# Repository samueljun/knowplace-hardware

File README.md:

sr-sryrs_home_automation
========================

CS 130 Sr. Sryrs Home Automation IBM Project

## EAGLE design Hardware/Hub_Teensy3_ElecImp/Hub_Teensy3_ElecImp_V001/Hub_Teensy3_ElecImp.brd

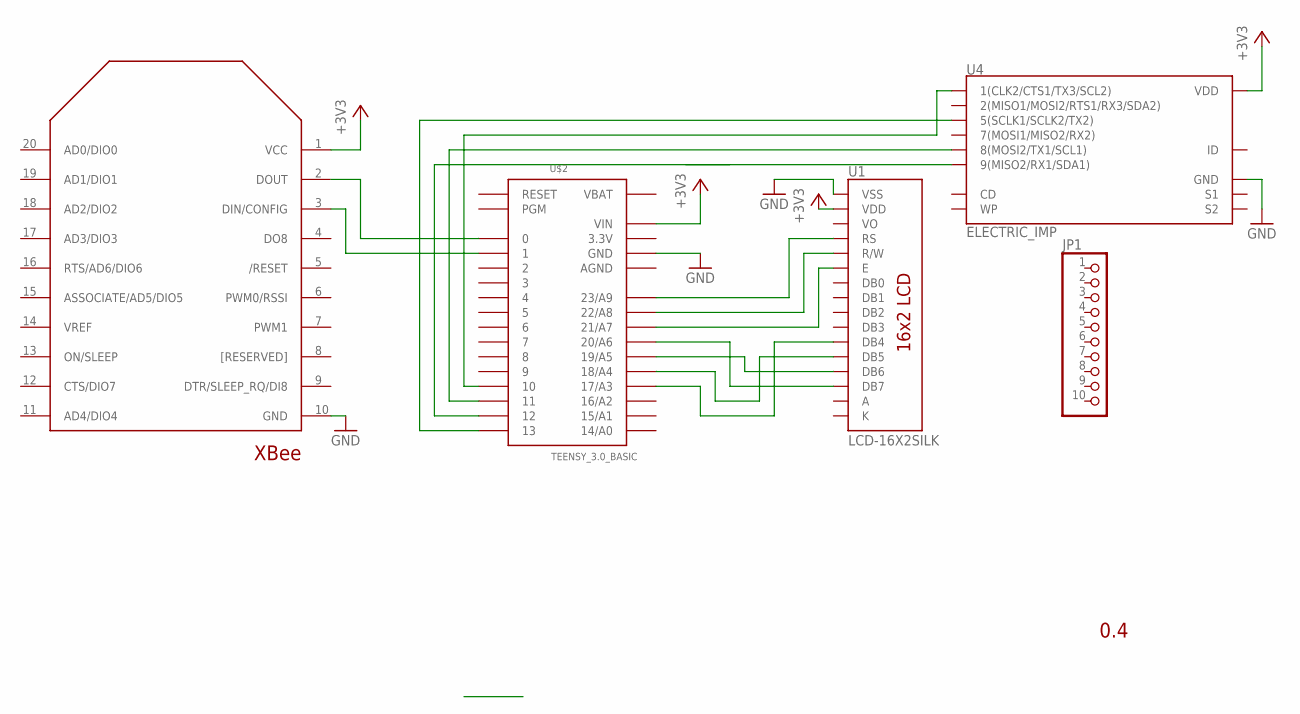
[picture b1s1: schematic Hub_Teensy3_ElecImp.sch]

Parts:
JP1: PINHD-1X10; 1X10
U1: LCD-16X2SILK; LCD-16X2
U4: ELECTRIC_IMP; SD_MMC_SOCKET
U$1: XBEE
U$2: TEENSY_3.0_BASIC

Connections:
3.3V: U$2.3.3V, U$2.3.3V1 (3.3V)
+3V3: U1.2 (VDD), U4.4 (VDD), U$1.1 (VCC), U$2.VIN
A: U1.15 (A)
AGND: U$2.AGND
GND: U1.1 (VSS), U4.3 (GND), U$1.10 (GND), U$2.GND, U$2.GND1 (GND)
K: U1.16 (K)
unnamed: U1.14 (DB7), U$2.20/A6
unnamed: U1.13 (DB6), U$2.19/A5
unnamed: U1.12 (DB5), U$2.18/A4
unnamed: U1.6 (E), U$2.21/A7
unnamed: U1.4 (RS), U$2.23/A9
unnamed: U1.5 (R/W), U$2.22/A8
unnamed: U4.5 (5(SCLK1/SCLK2/TX2)), U$2.13
unnamed: U4.1 (1(CLK2/CTS1/TX3/SCL2)), U$2.10
unnamed: U1.11 (DB4), U$2.17/A3
unnamed: U4.9 (9(MISO2/RX1/SDA1)), U$2.12
unnamed: U$1.3 (DIN/CONFIG), U$2.1
unnamed: U4.8 (8(MOSI2/TX1/SCL1)), U$2.11
unnamed: U$1.2 (DOUT), U$2.0
VBAT: U$2.VBAT

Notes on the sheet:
0.4

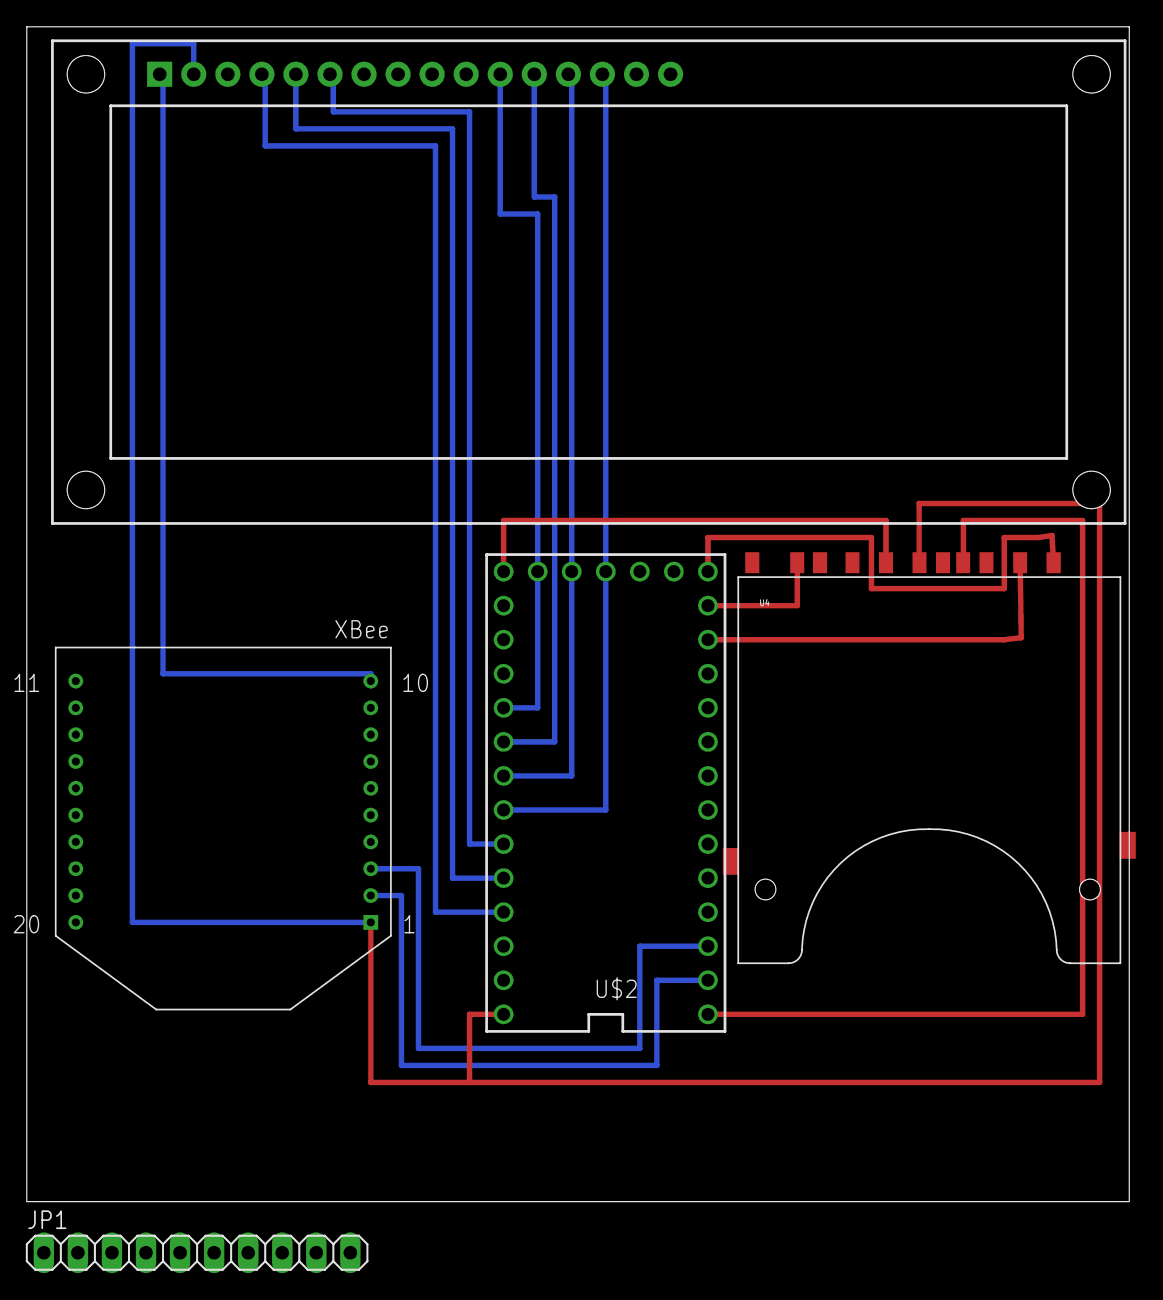
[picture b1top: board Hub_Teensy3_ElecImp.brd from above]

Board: 2 copper layers, 82.2 x 87.6 mm, 5 parts (0 on the bottom side), 16 nets.

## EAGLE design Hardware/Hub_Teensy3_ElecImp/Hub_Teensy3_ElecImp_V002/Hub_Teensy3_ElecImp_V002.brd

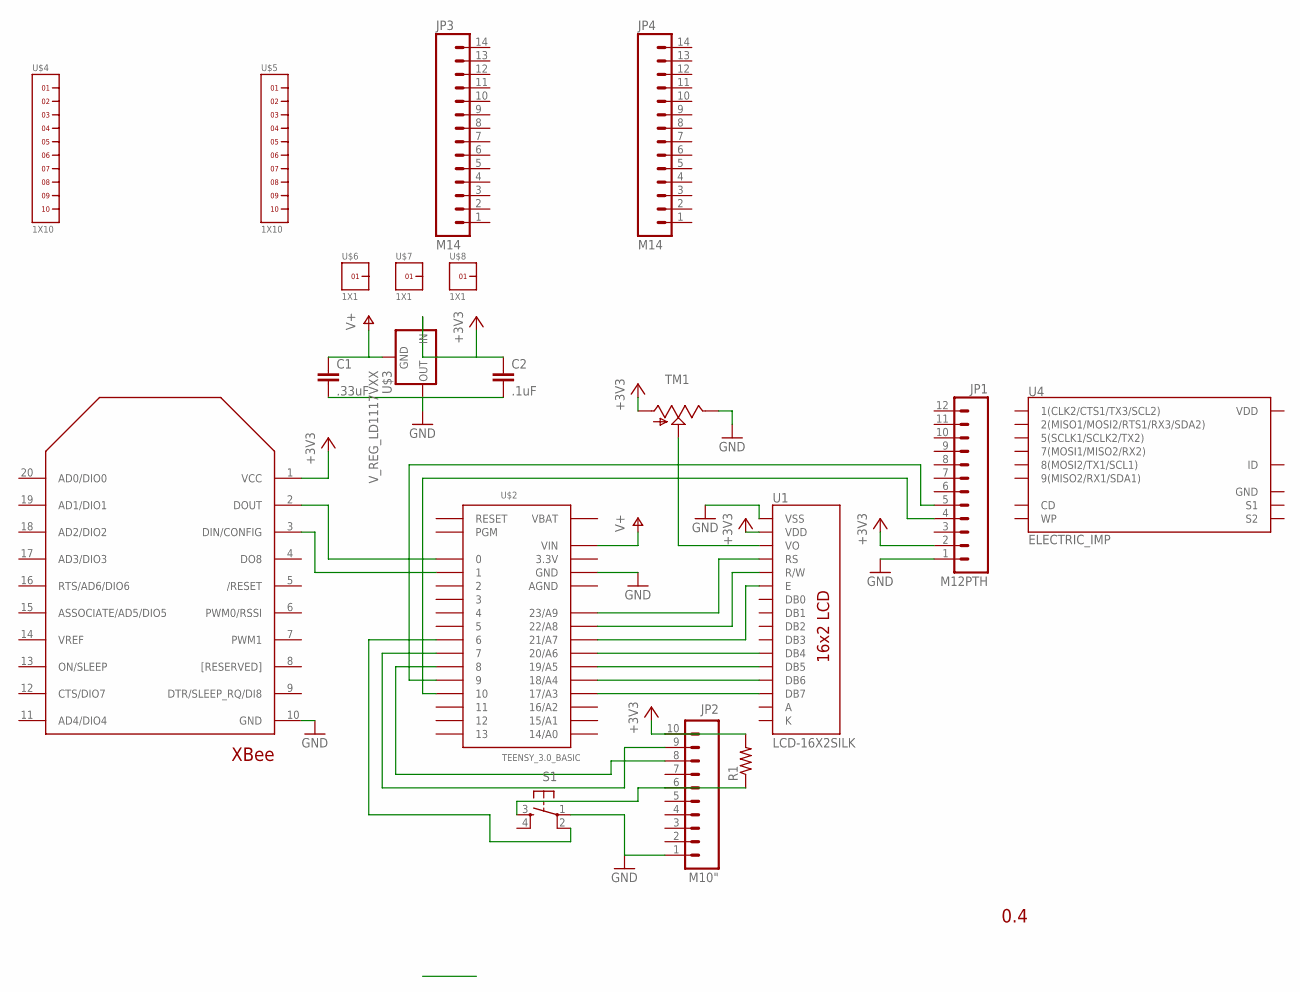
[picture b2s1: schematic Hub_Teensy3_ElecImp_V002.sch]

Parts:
C1: .33uF; 0805
C2: .1uF; 0805
JP1: M12PTH; 1X12
JP2: M10"; 1X10
JP3, JP4: M14; 1X14
R1: RESISTORPTH-1/4W; AXIAL-0.4
S1: TAC_SWITCHPTH; TACTILE-PTH
TM1: TRIM; 6MM
U1: LCD-16X2SILK; LCD-16X2
U4: ELECTRIC_IMP; SD_MMC_SOCKET
U$1: XBEE
U$2: TEENSY_3.0_BASIC
U$3: V_REG_LD1117VXX; 78XXL
U$4, U$5: 1X10
U$6, U$7, U$8: 1X1

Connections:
3.3V: U$2.3.3V, U$2.3.3V1 (3.3V)
+3V3: C2.1, JP1.2, JP2.10, R1.P$2 (2), TM1.A, U1.2 (VDD), U$1.1 (VCC), U$3.OUT (IN)
A: U1.15 (A)
AGND: U$2.AGND
GND: C1.2, C2.2, JP1.1, JP2.1, S1.1, TM1.E, U1.1 (VSS), U$1.10 (GND), U$2.GND, U$2.GND1 (GND), U$3.GND (OUT)
K: U1.16 (K)
unnamed: U1.11 (DB4), U$2.20/A6
unnamed: U1.12 (DB5), U$2.19/A5
unnamed: U1.13 (DB6), U$2.18/A4
unnamed: U1.6 (E), U$2.21/A7
unnamed: U1.4 (RS), U$2.23/A9
unnamed: U1.5 (R/W), U$2.22/A8
unnamed: JP1.5, U$2.9
unnamed: JP1.4, U$2.10
unnamed: U1.14 (DB7), U$2.17/A3
unnamed: JP2.8, U$2.8
unnamed: U$1.3 (DIN/CONFIG), U$2.1
unnamed: JP2.9, U$2.7
unnamed: TM1.S, U1.3 (VO)
unnamed: U$1.2 (DOUT), U$2.0
unnamed: JP2.6, R1.P$1 (1), S1.3
unnamed: S1.2, U$2.6
V+: C1.1, U$2.VIN, U$3.IN (GND)
VBAT: U$2.VBAT

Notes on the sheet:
0.4

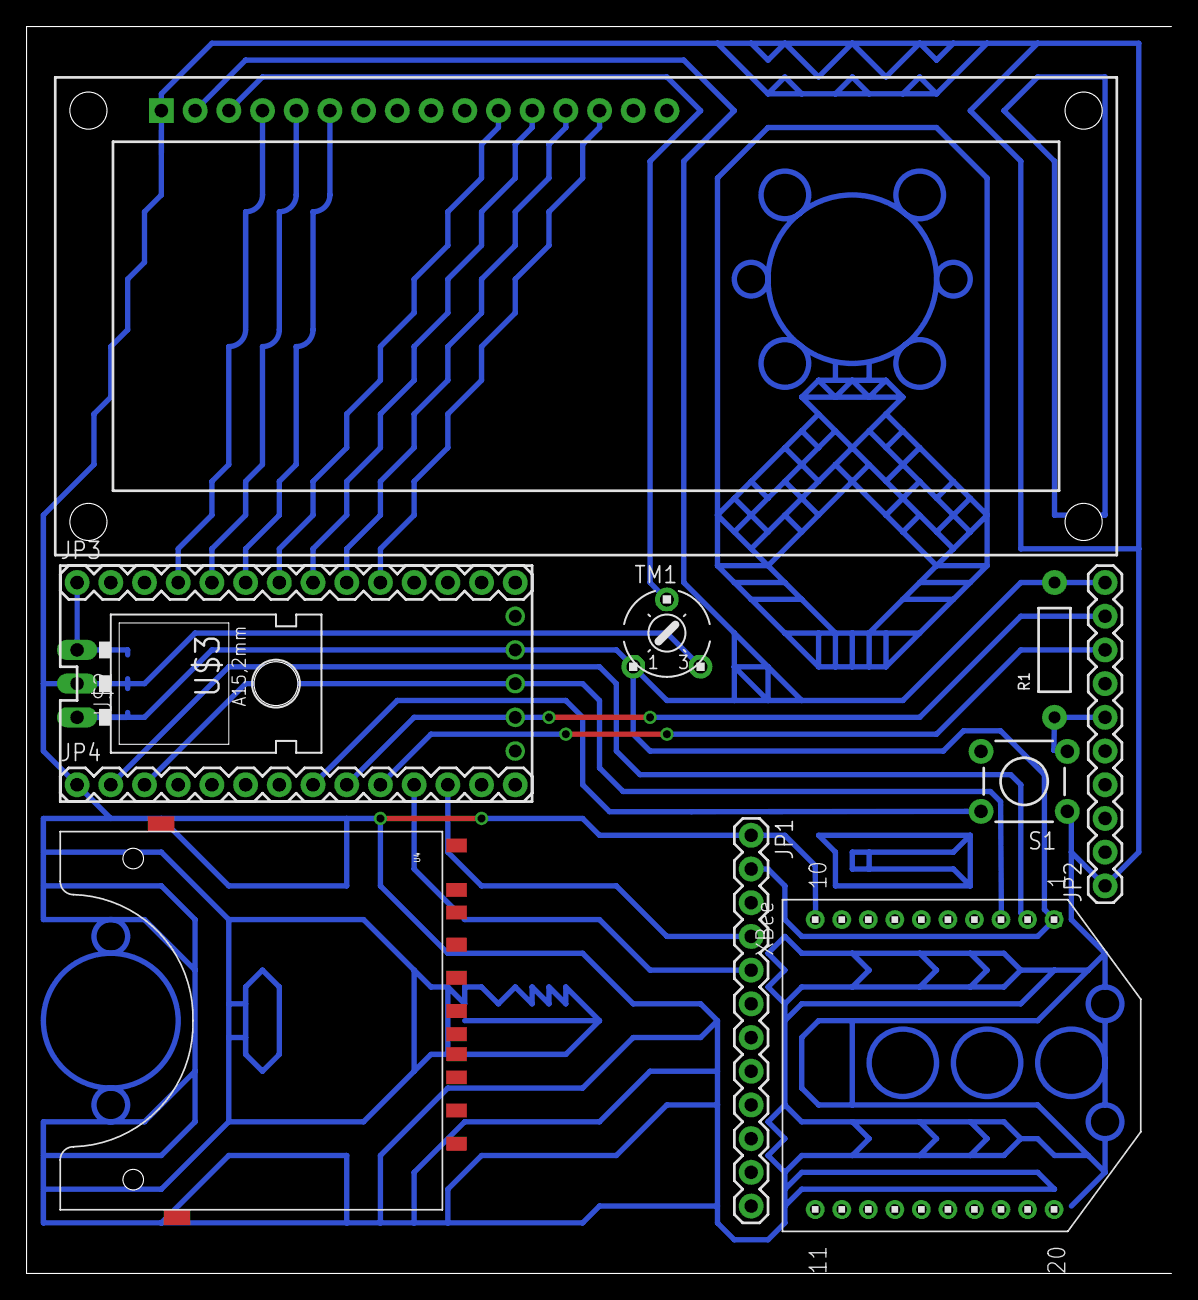
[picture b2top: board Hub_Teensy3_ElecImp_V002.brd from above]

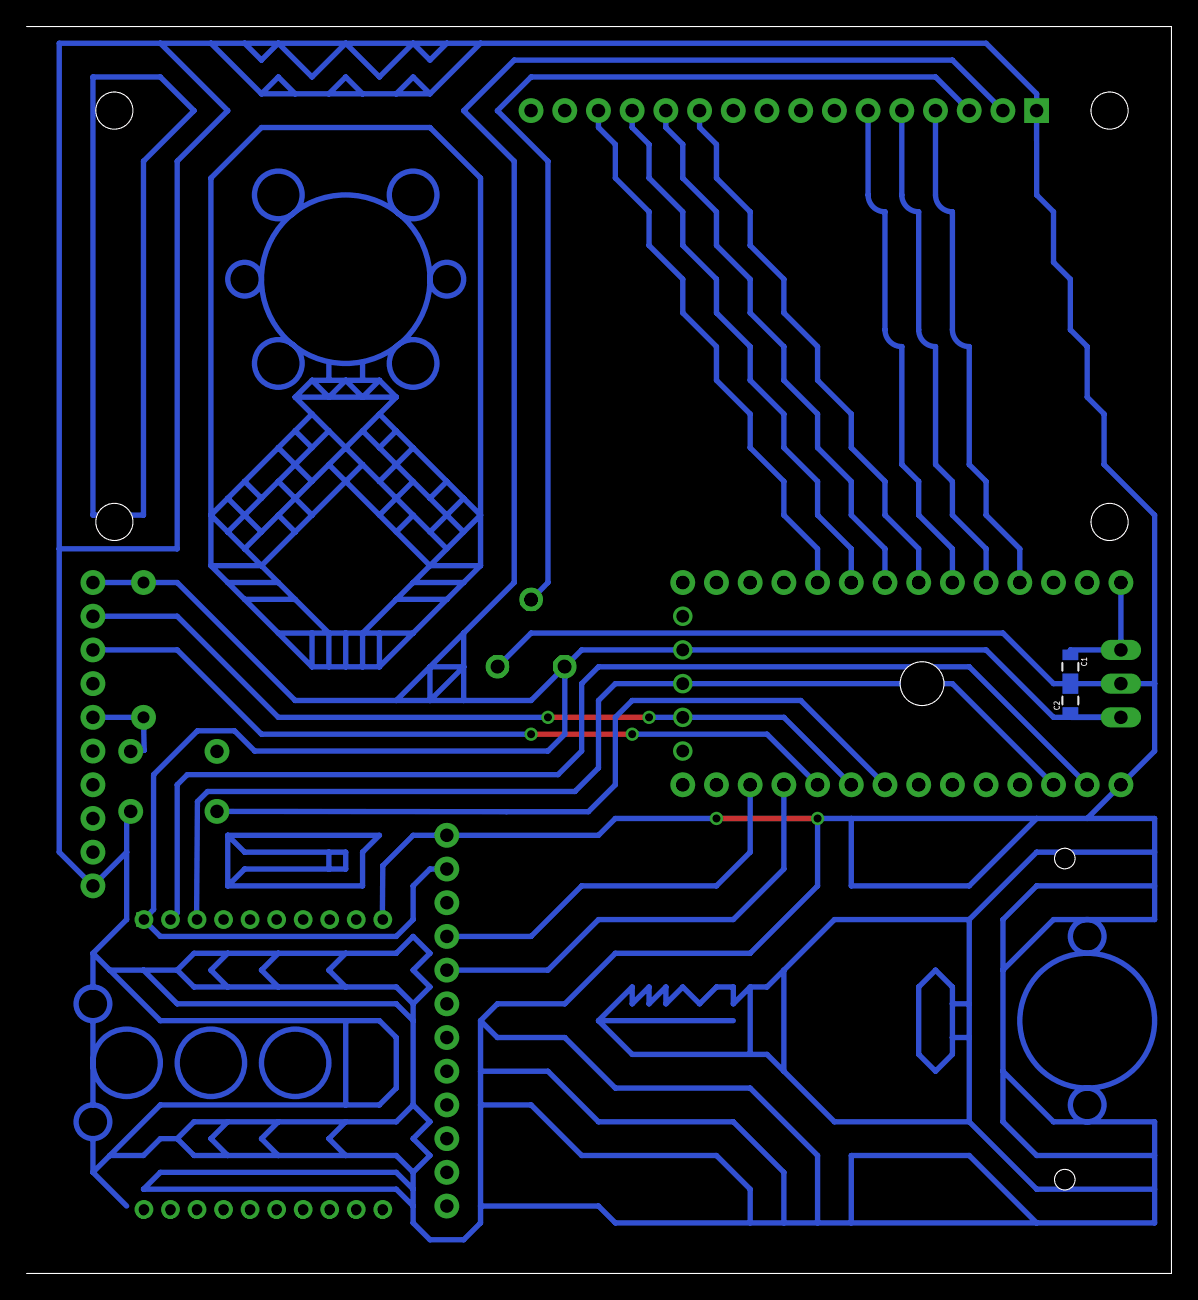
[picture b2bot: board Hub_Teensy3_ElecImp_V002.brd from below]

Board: 2 copper layers, 86.3 x 94.0 mm, 19 parts (2 on the bottom side), 20 nets.

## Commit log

2013-04-19 Create SR-SRYRS_Hub.ino
    Hardware:
    Teensy 2.0 (3.3v)
    Adafruit OLED (3.3v)
    WIZ811MJ Rev1.1 Ethernet Controller (3.3v)
    XBee Series 2 (3.3v)
    PanID: 1AAA
2013-04-23 Added Basic SQL Create Commands
    Needs to be checked and expanded on
2013-04-23 Changed data type for node and hub ids to VARCHAR
2013-04-26 Made Changes based on the 'Database Scribbles' doc
    I added a few things based on Ryan's 'Database Scribbles' google doc. I
    mainly added a few parameters that I was missing. I also added a Pins
    table between the Nodes and Data layer because I didn't realize that
    each Node can have multiple pins.
2013-04-29 Initial upload of SrSryrsHub library
2013-04-30 Replaced symbolic link with actual directories and files
2013-05-06 XBee now supported in the hub class
2013-05-12 Draft 1 of UI based on PivotalTracker
2013-05-15 Modification to details
2013-05-22 added Roger's get and post
2013-05-22 separated variables and values into two arrays
2013-05-22 Changed Serial to hubSerial
2013-05-22 Added print statement for values to hubSerial
2013-05-22 Added getDeviceStatus
2013-05-22 fixed error with adding Roger's code to the SrSryrsHub library
2013-05-22 fixed error introduced by adding Roger's functions
2013-05-23 milestone 2, can select the simple address of a node and send command to XBee node
2013-05-27 Added ethernetConnectAndPost method
2013-05-29 renamed SrSryrsHub to KnowPlaceHub, added option for adding new node using hardware
2013-05-30 added function addNewNodeToWeb and helper functions, broke up read and post functions
2013-06-02 added json replacement for ethernetReadPage
2013-06-05 added pwm node output
2013-06-06 added condition for using Processing as internet source
2013-06-06 Added Push for Json objects
2013-06-07 it fucking works: added own json parser for H L C T
2013-06-07 it work! had to code own json parser for parameters H L C T
2013-06-07 minor changes for final demo
2013-06-27 started PCBs for Teensy3
2013-06-27 on the way to generalizing an internet class

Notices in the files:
parts and their libraries:
SparkFun-Displays: Licensing: CC v3.0 Share-Alike You are welcome to use this library for commercial purposes.
